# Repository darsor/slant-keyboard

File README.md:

# Slant Keyboard

I liked the idea of the Corne or Sweep keyboards, but I didn't like the microcontroller hanging on the side. So I designed my own with a small 7.5 degree tent (Slant), making enough room for a nice!nano and a larger 350 mAh battery to go underneath the PCB.

The case is custom designed and printed. I used Onshape to CAD the entire design, which really helped everything work together on the first try. You can find the onshape model [here](https://cad.onshape.com/documents/52d8c97deb1f4fedd7779345/w/a823d43323299a2b5f12e80a/e/73bc7d91904b86f6c9de98d1).

PCB and key placement were aided by Ergogen, which simplified things quite a bit. Kicad was used for the layout and routing.

This repository contains:
* ergopad/: screenshots from ergopad to help fit the physical key placement to my hand
* kicad_project/: the PCB files
* parts/: a digikey parts list
* zmk-config/: the ZMK firmware files, including keymap

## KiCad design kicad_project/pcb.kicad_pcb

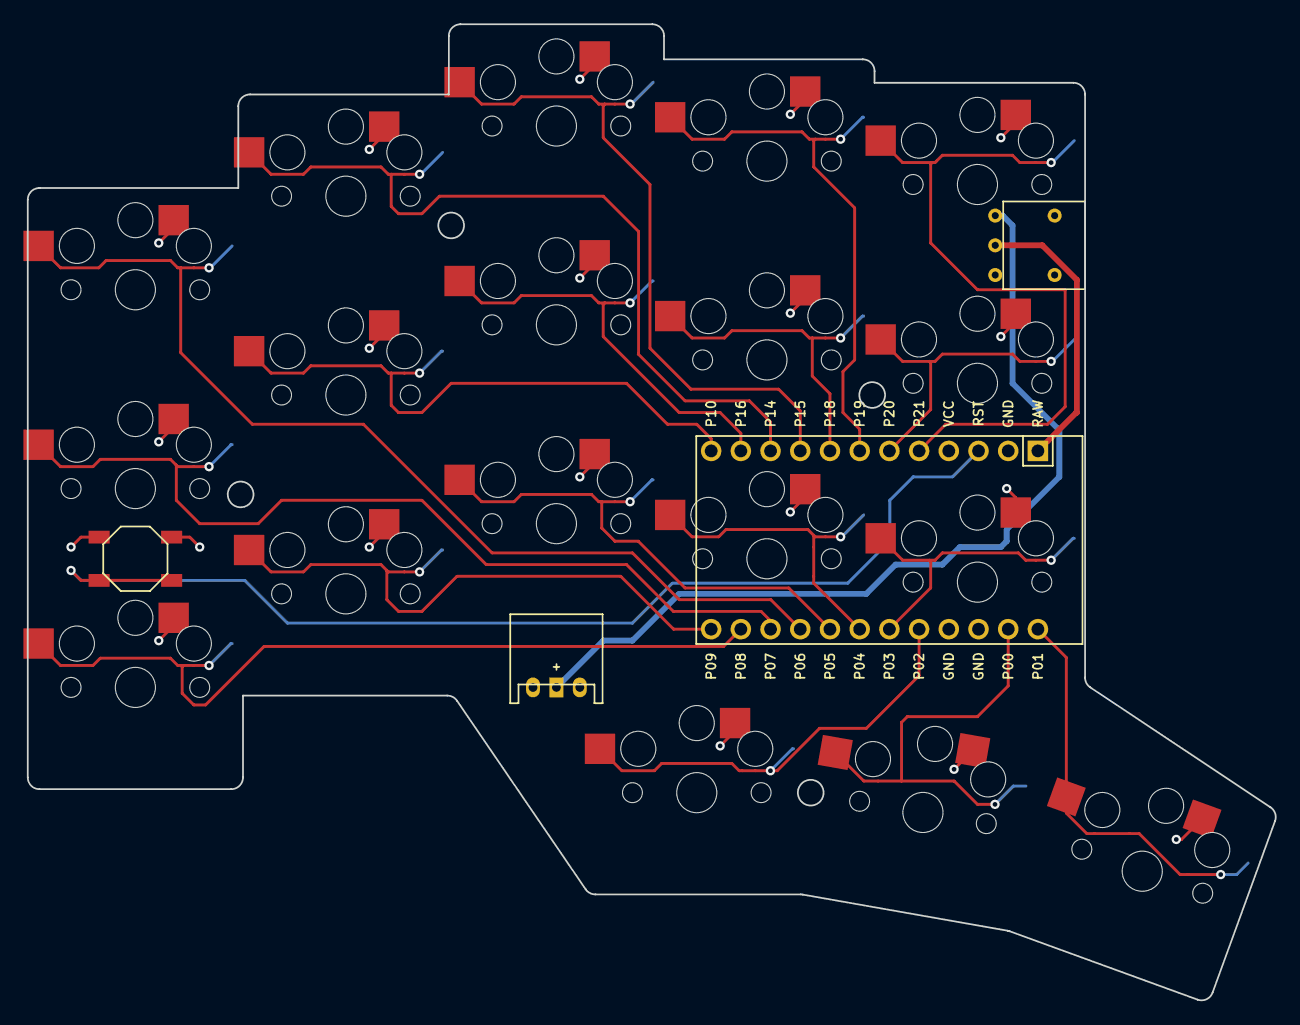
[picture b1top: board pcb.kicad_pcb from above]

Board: 2 copper layers, 106.7 x 83.5 mm, 23 parts (0 on the bottom side), 22 nets.

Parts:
B1, B2: SW_TACT_ALPS_SKQGABE010
JST1: JST_PH_S2B-PH-K_02x2.00mm_Angled
MCU1: ProMicro
S1, S2, S3, S4, S5, S6, S7, S8, S9, S10, S11, S12, S13, S14, S15, S16, S17, S18: PG1350
T1: GW12RHH

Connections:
GND: B1.1, B2.1, JST1.2, MCU1.2, MCU1.15, MCU1.16, S1.1, S2.1, S3.1, S4.1, S5.1, S6.1, S7.1, S8.1, S9.1, S10.1, S11.1, S12.1, S13.1, S14.1, S15.1, S16.1, S17.1, S18.1
RST: B1.2, B2.2, MCU1.3
matrix_index_bottom: MCU1.19, S10.2
matrix_index_home: MCU1.8, S11.2
matrix_index_top: MCU1.7, S12.2
matrix_inner_bottom: MCU1.18, S13.2
matrix_inner_home: MCU1.6, S14.2
matrix_inner_top: MCU1.5, S15.2
matrix_middle_bottom: MCU1.20, S7.2
matrix_middle_home: MCU1.11, S8.2
matrix_middle_top: MCU1.9, S9.2
matrix_pinky_bottom: MCU1.23, S1.2
matrix_pinky_home: MCU1.22, S2.2
matrix_pinky_top: MCU1.21, S3.2
matrix_ring_bottom: MCU1.24, S4.2
matrix_ring_home: MCU1.12, S5.2
matrix_ring_top: MCU1.10, S6.2
thumb_left: MCU1.17, S16.2
thumb_mid: MCU1.14, S17.2
thumb_right: MCU1.13, S18.2
vbattp: JST1.1, T1.4
vbattp_sw: MCU1.1, T1.5

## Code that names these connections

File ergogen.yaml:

units:
  choc_cutout: 13.80
  gap: 0.2
  screw_radius: 1.1
  # size of key with gap on all sides
  kx: cx + 2*gap
  ky: cy + 2*gap
  ring_stagger: 8
  middle_stagger: 6
  index_stagger: -3
  inner_stagger: -2
  corner: 1
  # tan(5 degrees), where 5 is half the rotation of the thumb keys
  thumb_tan: 0.087488664
points:
  zones:
    matrix:
      columns:
        pinky.spread: cx
        ring.stagger: ring_stagger
        ring.spread: cx
        middle.stagger: middle_stagger
        middle.spread: cx
        index.stagger: index_stagger
        index.spread: cx
        inner.stagger: inner_stagger
        inner.spread: cx
      rows:
        bottom.padding: cy
        home.padding: cy
        top.padding: cy
    thumb:
      anchor:
        ref: matrix_index_bottom
        shift: [-6, -20]
        rotate: 0
      columns:
        left:
          key.name: thumb_left
        mid:
          spread: cx
          rotate: -10
          origin: [-0.5cx, -0.5cy]
          key.name: thumb_mid
        right:
          spread: cx
          rotate: -10
          origin: [-cx/2, -cy/2]
          key.name: thumb_right
  key:
    footprints:
      choc:
        type: choc
        nets:
          from: GND
          to: =name
        params:
          hotswap: true
          reverse: true
          keycaps: true
outlines:
  exports:
    keys:
      - type: keys
        side: left
        size: [cx, cy]
    screw_holes:
      top_left:
          type: circle
          anchor:
            ref: matrix_ring_home
            shift: [-cx/2, -cy/2]
          radius: screw_radius
      top:
        $extends: outlines.exports.screw_holes.top_left
        anchor.ref: matrix_middle_top
        anchor.shift: [-cx/2, -cy/2]
      right:
        $extends: outlines.exports.screw_holes.top_left
        anchor.ref: matrix_inner_home
        anchor.shift: [-cx/2, -1]
      bottom:
        $extends: outlines.exports.screw_holes.top_left
        anchor.ref: thumb_left
        anchor.shift: [cx/2+cy/2*thumb_tan, 0]
    definitions:
      $skip: true
      # column containing the outline of all three keys, with padding and rounded corners
      # top key centered at anchor ref
      column:
        type: rectangle
        size: [kx, 2*cy + ky - ycutoff]
        anchor.ref: matrix_pinky_top
        anchor.shift: [-kx/2 + xshift, -(2*cy + ky - ycutoff) + ky/2]
        corner: corner
        # shift by x, cut off y amount from bottom
        $params: [xshift, ycutoff]
        $args: [0, 0]
    thumb:
      - type: polygon
        points:
          - ref: matrix_ring_bottom
            shift: [0, ky/2]
          - shift: [0, -ky]
          - ref: matrix_ring_bottom
            shift: [kx/2, -ky/2]
          - ref: thumb_left
            shift: [-kx/2, -ky/2]
          - ref: thumb_left
            # tan(10/2) = 0.087, where 10 is the angle between thumb keys
            shift: [cx/2-thumb_tan*gap, -ky/2]
          - ref: thumb_right
            shift: [-cx/2+thumb_tan*gap, -ky/2]
          - ref: thumb_right
            shift: [kx/2, -ky/2]
          - ref: thumb_right
            shift: [kx/2, ky/2]
          - ref: matrix_inner_bottom
            shift: [kx/2, -ky/2]
          - shift: [0, ky]
    main_outline:
      # column extensions fill in gaps between columns
      pinky_col:
        $extends: outlines.exports.definitions.column
        anchor.ref: matrix_pinky_top
      pinky_col_ext:
        $extends: outlines.exports.main_outline.pinky_col
        $args: [cx/2, ring_stagger]
      ring_col:
        $extends: outlines.exports.definitions.column
        anchor.ref: matrix_ring_top
      ring_col_ext:
        $extends: outlines.exports.main_outline.ring_col
        $args: [cx/2, middle_stagger]
      middle_col:
        $extends: outlines.exports.definitions.column
        anchor.ref: matrix_middle_top
      index_col:
        $extends: outlines.exports.definitions.column
        anchor.ref: matrix_index_top
      index_col_ext:
        $extends: outlines.exports.main_outline.index_col
        $args: [-cx/2, -index_stagger]
      inner_col:
        $extends: outlines.exports.definitions.column
        anchor.ref: matrix_inner_top
      inner_col_ext:
        $extends: outlines.exports.main_outline.inner_col
        $args: [-cx/2, -inner_stagger]
      thumb:
        name: thumb
        fillet: corner
    pcb_outline:
      - name: main_outline
      - name: screw_holes
        operation: subtract
    top_plate:
      - name: main_outline
      - name: screw_holes
        operation: subtract
      - type: keys
        side: left
        size: choc_cutout
        operation: subtract
cases:
  top_plate:
    - type: outline
      name: top_plate
      extrude: 1.2
pcbs:
  pcb:
    outlines.outline.outline: pcb_outline
    footprints:
      nicenano:
        type: promicro
        anchor:
          - ref: matrix_inner_bottom
            shift: [-cx/2+gap, 3.6]
            rotate: 180
        nets:
          RAW: vbattp_sw
          GND: GND
          RST: RST
          P21: matrix_inner_top
          P20: matrix_inner_home
          P19: matrix_index_top
          P18: matrix_index_home
          P15: matrix_middle_top
          P14: matrix_ring_top
          P16: matrix_middle_home
          P10: matrix_ring_home
          P1: thumb_right
          P0: thumb_mid
          P2: thumb_left
          P3: matrix_inner_bottom
          P4: matrix_index_bottom
          P5: matrix_middle_bottom
          P6: matrix_pinky_top
          P7: matrix_pinky_home
          P8: matrix_pinky_bottom
          P9: matrix_ring_bottom
      power_switch:
        type: GW12RHH
        anchor:
          - ref: matrix_inner_top
            shift: [kx/2, -5.2]
            rotate: -90
        nets:
          from: vbattp
          to: vbattp_sw
      battery_plug:
        type: jstph_3pin
        anchor:
          - ref: matrix_middle_bottom
            shift: [0, -14]
            rotate: 180
        nets:
          pos: vbattp
          neg: GND
      reset_button_top:
        type: button
        anchor: 
          - ref: matrix_pinky_home
            shift: [0, -6]
        nets:
          from: GND
          to: RST
        params.side: F
      reset_button_bottom:
        $extends: pcbs.pcb.footprints.reset_button_top
        params.side: B

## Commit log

2022-11-07 Initial User Config.
2022-11-07 initial Slant configuration
2022-11-21 added ergogen and kicad files
2022-11-21 attempt to fix workflow build
2022-11-21 attempt 2 to fix github workflow
2022-11-21 filled out default keymap
2022-11-21 moved behaviors before keymap
2022-11-21 missing semicolon
2022-11-21 syntax error
2022-11-21 fixed GUI keycode
2022-11-21 added apostrophe, grave, and capsword
2022-11-21 fixed capsword keys
2022-11-28 updated keymap
2022-11-28 balanced and tap prefered mods, output toggle
2022-11-28 longer alt hold duration
2022-11-28 reduce caps word combo time
2022-11-28 removed alt hold on N key
2022-11-29 rearranged symbols
2022-12-02 changed shift back to hold-preferred, can also alternate sym/num layers
2022-12-13 must double tap all bluetooth keys
2022-12-19 added parts list
2023-01-09 fix bluetooth double-tap
2023-01-09 fix bluetooth double-tap 2
2023-01-09 fix bluetooth double-tap 3
2023-01-09 fix bluetooth double-tap 4
2023-01-09 fix bluetooth double-tap 5
2023-01-09 double-tap guard output toggle
2023-01-09 sym layer activated by using both num and nav layers
2023-01-09 removed trailing backslash
2023-01-09 tap-hold backspace to enable repeat
2023-08-03 update to zephyr 3.2, hold RET when double tapped
2023-08-03 work around windows bluetooth battery reporting bug
2023-08-03 fix left shift underscore
